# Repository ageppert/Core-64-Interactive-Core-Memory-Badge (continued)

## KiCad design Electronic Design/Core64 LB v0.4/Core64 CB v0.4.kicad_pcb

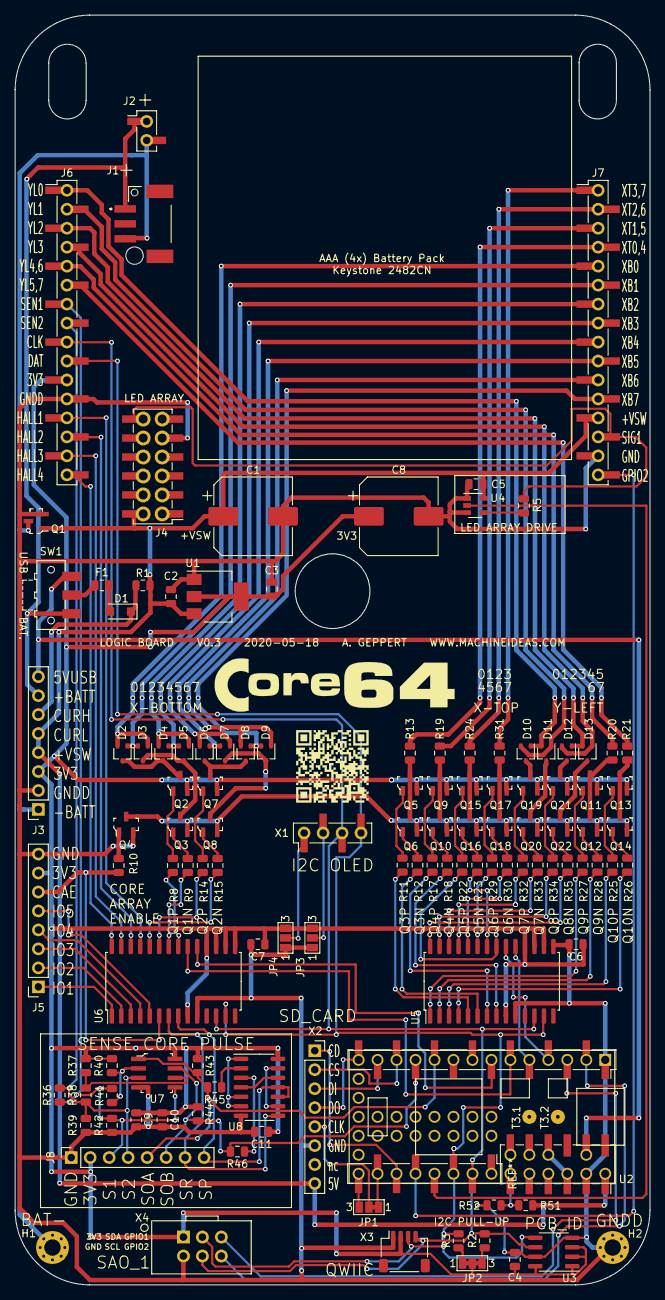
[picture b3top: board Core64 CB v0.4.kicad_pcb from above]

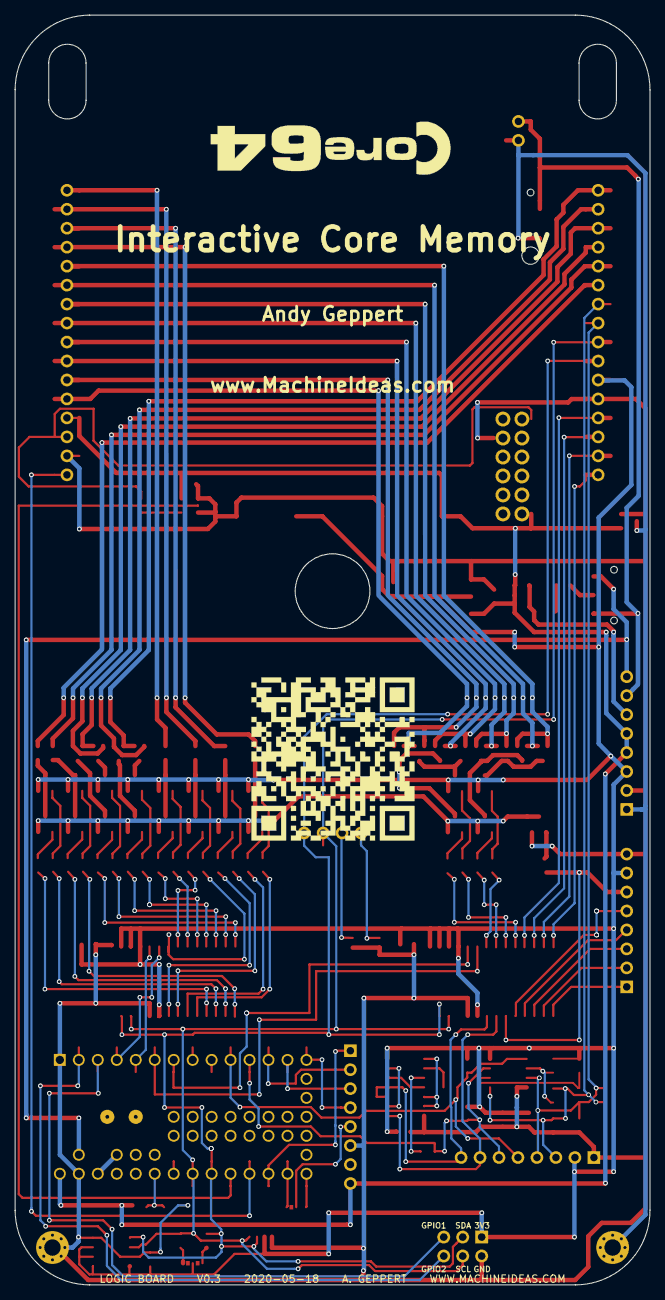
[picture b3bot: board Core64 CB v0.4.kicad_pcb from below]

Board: 2 copper layers, 85.0 x 170.0 mm, 122 parts (2 on the bottom side), 131 nets.

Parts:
C1, C8: 1000uF; CP_Elec_10x10
C2, C4, C5, C6, C7, C9, C11: 0.1uF; C_0805_2012Metric
C3, C10: 10uF; C_0805_2012Metric
D1: MBR120; D_SOD-123F
D2, D4, D6, D8, D10, D12: BAT54AW; SOT-323_SC-70
D3, D5, D7, D9, D11, D13: BAT54CW; SOT-323_SC-70
F1: Polyfuse; Fuse_0805_2012Metric
H1: -BATT PAD; MountingHole_2.2mm_M2_Pad_Via
H2: GND PAD; MountingHole_2.2mm_M2_Pad_Via
J1: BM03B-PASS-1-TFT__LF__SN_; BM03BPASS1TFTLFSN
J2: Conn_01x02_Male; PinSocket_1x02_P2.54mm_Vertical_SMD_Pin1Left
J3, J5, J8: Conn_01x08_Female; PinSocket_1x08_P2.54mm_Vertical
J4: TSM-106-03-T-DV‎; PinHeader_2x06_P2.54mm_Vertical_SMD_and_TH
J6, J7: SSW-116-22-F-S-VS‎; PinHeader_1x16_P2.54mm_Vertical_SMD_and_TH_Pin1Left
JP1: SolderJumper_3_Bridged12; SolderJumper-3_P1.3mm_Bridged12_Pad1.0x1.5mm_NumberLabels
JP2: SolderJumper_3_Bridged123; SolderJumper-3_P1.3mm_Bridged123_Pad1.0x1.5mm_NumberLabels
JP3, JP4: SolderJumper_3_Open; SolderJumper-3_P1.3mm_Open_Pad1.0x1.5mm_NumberLabels
L1, L2: Core_64_Logo; Core64_Logo
L3: Core_64_Github_Link; Github_Link_Large
L4: Core_64_Github_Link; Github_Link_Small
Q1: IRLML6344TRPBF; SOT-23-3
Q2, Q5, Q7, Q9, Q11, Q13, Q15, Q17, Q19, Q21: MMBT4403LT1G; SOT-23-3
Q3, Q4, Q6, Q8, Q10, Q12, Q14, Q16, Q18, Q20, Q22: MMBT4401LT1G; SOT-23-3
R1: 0.001; R_0805_2012Metric
R2, R3: 4K7; R_0805_2012Metric
R5: 300; R_0805_2012Metric
R8, R9, R10, R11, R12, R14, R15, R17, R18, R22, R23, R25, R26, R27, R28, R29, R30, R32, R33, R34, R35: 470; R_0805_2012Metric
R13, R19, R20, R21, R24, R31: 6R8; R_0805_2012Metric
R36, R39, R42: 1K5; R_0805_2012Metric
R37, R40: 1K8; R_0805_2012Metric
R38, R41: 11; R_0805_2012Metric
R43, R44, R45, R46, R51, R52: 10k; R_0805_2012Metric
SW1: JS102011SAQN; SW_SPDT_CK-JS102011SAQN
U1: LD1117S33TR_SOT223; SOT-223-3_TabPin2
U2: Teensy-LC; Teensy30_31_32_LC_SMD_SOCKETS
U3: M24C01-RMN; SOIC-8_3.9x4.9mm_P1.27mm
U4: SN74LV1T125DBVR; SOT-23-5
U5, U6: MCP23017_SO; SOIC-28W_7.5x17.9mm_P1.27mm
U7: LM393; SOIC-8_W3.9mm
U8: 74HC02; SOIC-14_3.9x8.7mm_P1.27mm
X1: SSW-104-22-L-S-VS; PinSocket_1x04_P2.54mm_Vertical_SMD_and_TH_Pin1Left
X2: Conn_01x08_Female; PinSocket_1x08_P2.54mm_Vertical
X3: Conn_01x04_Male; JST_SH_SM04B-SRSS-TB_1x04-1MP_P1.00mm_Horizontal
X4: SAO_conn_SFH11-NBPC-D03-ST-BK; Badgelife-SAOv169-BADGE-2x3

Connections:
3V3_800mA: C3.1, C4.1, C6.1, C7.1, C8.1, C9.1, C10.1, C11.1, J3.3, J5.7, J6.11, J8.2, JP2.2, JP3.3, JP4.3, Q2.2, Q5.2, Q7.2, Q9.2, Q11.2, Q13.2, Q15.2, Q17.2, Q19.2, Q21.2, R37.1, R40.1, R43.1, R44.1, U1.2, U3.1, U3.2, U3.3, U3.8, U5.9, U5.16, U5.17, U5.18, U6.9, U6.15, U6.16, U6.17, U6.18, U7.8, U8.14, X3.2, X4.1
5V_USB: J3.8, SW1.1, U2.34
+BATT: J1.1, J2.1, J3.7, SW1.3
+VSW: C1.1, C2.1, C5.1, J3.4, J3.5, J4.2, J7.13, Q1.1, R1.2, R51.1, U1.3, U2.33, U4.5, X2.8
-BATT: H1.1, J1.3, J2.2, J3.1, Q1.3
CUR_HI: D1.1, J3.6, R1.1
GNDPWR: Q3.2, Q4.3, Q6.2, Q8.2, Q10.2, Q12.2, Q14.2, Q16.2, Q18.2, Q20.2, Q22.2
HALL_SWITCH_1: J6.13, U6.25
HALL_SWITCH_2: J6.14, U6.26
HALL_SWITCH_3: J6.15, U6.27
HALL_SWITCH_4: J6.16, U6.28
I2C_CLOCK: J6.9, R2.2, U2.26, U3.6, U5.12, U6.12, X1.3, X3.4, X4.4
I2C_DATA: J6.10, R3.2, U2.25, U3.5, U5.13, U6.13, X1.4, X3.3, X4.3
IOEXP_ID32_INT_A: U2.4, U5.20
IOEXP_ID32_INT_B: U2.5, U5.19
IOEXP_ID33_INT_A: U2.6, U6.20
IOEXP_ID33_INT_B: U2.7, U6.19
LED_MATRIX_3V3_SIG: U2.24, U4.2
LED_MATRIX_+VSW_SIG: J4.12, J7.14, R5.2
unnamed: D1.2, F1.1
unnamed: D2.3, D4.3, Q2.3
unnamed: D3.3, D5.3, Q3.3
unnamed: D6.3, D8.3, Q7.3
unnamed: D7.3, D9.3, Q8.3
unnamed: D10.3, Q19.3
unnamed: D11.3, Q20.3
unnamed: D12.3, Q21.3
unnamed: D13.3, Q22.3
unnamed: F1.2, SW1.2
unnamed: JP1.1, U2.21
unnamed: JP1.3, U2.20
unnamed: JP2.1, R3.1
unnamed: JP2.3, R2.1
unnamed: JP3.2, X1.2
unnamed: JP4.2, X1.1
unnamed: Q2.1, R8.1
unnamed: Q3.1, R9.1
unnamed: Q4.1, R10.1
unnamed: Q5.1, R11.1
unnamed: Q5.3, Q6.3, R13.1
unnamed: Q6.1, R12.1
unnamed: Q7.1, R14.1
unnamed: Q8.1, R15.1
unnamed: Q9.1, R17.1
unnamed: Q10.1, R18.1
unnamed: Q9.3, Q10.3, R19.2
unnamed: Q11.1, R27.1
unnamed: Q11.3, Q12.3, R20.2
unnamed: Q12.1, R28.1
unnamed: Q13.1, R25.1
unnamed: Q13.3, Q14.3, R21.2
unnamed: Q14.1, R26.1
unnamed: Q15.1, R22.1
unnamed: Q15.3, Q16.3, R24.2
unnamed: Q16.1, R23.1
unnamed: Q17.1, R29.1
unnamed: Q17.3, Q18.3, R31.2
unnamed: Q18.1, R30.1
unnamed: Q19.1, R32.1
unnamed: Q20.1, R33.1
unnamed: Q21.1, R34.1
unnamed: Q22.1, R35.1
unnamed: R5.1, U4.4
unnamed: R37.2, R38.1, U7.6
unnamed: R40.2, R41.1, U7.2
unnamed: R45.1, U8.2
unnamed: R46.1, U8.3
unnamed: U8.1, U8.5, U8.6
unnamed: U8.4, U8.12
unnamed: U8.9, U8.13
Q1N: R9.2, U6.22
Q1P: R8.2, U6.21
Q2N: R15.2, U6.24
Q2P: R14.2, U6.23
Q3N: R12.2, U5.6
Q3P: R11.2, U5.5
Q4N: R18.2, U5.8
Q4P: R17.2, U5.7
Q5N: R23.2, U5.22
Q5P: R22.2, U5.21
Q6N: R30.2, U5.24
Q6P: R29.2, U5.23
Q7N: R33.2, U5.26
Q7P: R32.2, U5.25
Q8N: R35.2, U5.28
Q8P: R34.2, U5.27
Q9N: R28.2, U5.2
Q9P: R27.2, U5.1
Q10N: R26.2, U5.4
Q10P: R25.2, U5.3
SAO1_GPIO1(TX): U2.3, X4.5
SAO1_GPIO2(RX): U2.2, X4.6
SAO3_GPIO2: J7.16, U2.23
SD_CD: U2.22, X2.1
SD_CLK: JP1.2, X2.5
SD_CS: U2.12, X2.2
SD_DI: U2.13, X2.3
SD_DO: U2.14, X2.4
SENSE1: J6.7, J8.3, R36.1, R41.2, R42.1, U7.5
SENSE2: J6.8, J8.4, R36.2, R38.2, R39.1, U7.3
SENSE_OUT_A: J8.5, R43.2, R45.2, U2.10, U7.1
SENSE_OUT_B: J8.6, R44.2, R46.2, U2.11, U7.7
SENSE_PULSE: J8.8, U6.8, U8.10, U8.11
SENSE_RESET: J8.7, U6.7, U8.8
SPARE_1: J5.1, U6.1
SPARE_2: J5.2, U6.2
SPARE_3: J5.3, U6.3
SPARE_4: J5.4, U6.4
SPARE_5: J5.5, U6.5
TEENSY_3V3: U2.31, U2.35
TEENSY_GND: C1.2, C2.2, C3.2, C4.2, C5.2, C6.2, C7.2, C8.2, C9.2, C10.2, C11.2, H2.1, J3.2, J4.9, J5.8, J6.12, J7.15, J8.1, JP3.1, JP4.1, Q1.2, Q4.2, R39.2, R42.2, R52.2, U1.1, U2.1, U2.32, U3.4, U3.7, U4.1, U4.3, U5.10, U5.15, U6.10, U7.4, U8.7, X2.6, X3.1, X4.2
VSW_HALF_VOL_MONITOR: R51.2, R52.1, U2.28
WRITE_ENABLE: J5.6, R10.2, U6.6
XB0: D2.2, D3.1, J7.5
XB1: D2.1, D3.2, J7.6
XB2: D4.2, D5.1, J7.7
XB3: D4.1, D5.2, J7.8
XB4: D6.2, D7.1, J7.9
XB5: D6.1, D7.2, J7.10
XB6: D8.2, D9.1, J7.11
XB7: D8.1, D9.2, J7.12
XT0-4: J7.4, R13.2
XT1-5: J7.3, R19.1
XT2-6: J7.2, R24.1
XT3-7: J7.1, R31.1
YL0: D10.1, D11.2, J6.1
YL1: D10.2, D11.1, J6.2
YL2: D12.1, D13.2, J6.3
YL3: D12.2, D13.1, J6.4
YL4: J6.5, R20.1
YL5: J6.6, R21.1

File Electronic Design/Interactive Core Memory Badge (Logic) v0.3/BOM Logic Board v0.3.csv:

Source:,/Users/ageppert/Dropbox/Electronics/Core 64 Interactive Badge/Core-64-Interactive-Core-Memory-Badge/Electronic Design/Interactive Core Memory Badge (Logic) v0.3/Interactive Core Memory Badge (Logic) Main v0.3.sch,,,,,,,,,,,,,,,,,
Date:,"Thursday, May 21, 2020 at 07:06:58 AM",,,,,,,,,,,,,,,,,
Tool:,Eeschema (5.1.2-1)-1,,,,,,,,,,,,,,,,,
Generator:,/private/var/folders/kh/1q_kd4hn7cq821df7xpmdhbw0000gn/T/AppTranslocation/C0C9017D-E73E-48F9-99F9-451879B2E2B1/d/kicad.app/Contents/SharedSupport/plugins/bom_csv_grouped_by_value.py,,,,,,,,,,,,,,,,,
Component Count:,122,,,,,,,,,,,,,,,,,
,,,,,,,,,,,,,,,,,,
,,,,,,,,,,,,,,,,,,
Collated Components:,,,,,,,,,,,,,,,,,,
,,,,,,,,,,,,,,,,,,
Item,Qty,Reference(s),Value,Digi-Key_PN,LibPart,Footprint,Datasheet,Category,DK_Datasheet_Link,DK_Detail_Page,Description,Family,Height,MPN,Manufacturer,Manufacturer_Name,Manufacturer_Part_Number,Status
1,2,"C1, C8",1000uF,,Device:CP1_Small,Capacitor_SMD:CP_Elec_10x10,~,,,,,,,,,,,
2,7,"C2, C4, C5, C6, C7, C9, C11",0.1uF,,Device:CP1_Small,Capacitor_SMD:C_0805_2012Metric,~,,,,,,,,,,,
3,2,"C3, C10",10uF,,Device:CP1_Small,Capacitor_SMD:C_0805_2012Metric,~,,,,,,,,,,,
4,1,D1,MBR120,,Diode:MBR0520,Diode_SMD:D_SOD-123F,https://www.digikey.com/product-detail/en/on-semiconductor/M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,,,,,,,,,,,
5,6,"D2, D4, D6, D8, D10, D12",BAT54AW,,Diode:BAT54AW,Package_TO_SOT_SMD:SOT-323_SC-70,https://assets.nexperia.com/documents/data-sheet/BAT54W_SER.pdf,,,,,,,,,,,
6,6,"D3, D5, D7, D9, D11, D13",BAT54CW,,Diode:BAT54CW,Package_TO_SOT_SMD:SOT-323_SC-70,https://assets.nexperia.com/documents/data-sheet/BAT54W_SER.pdf,,,,,,,,,,,
7,1,F1,Polyfuse,,Device:Polyfuse,Fuse:Fuse_0805_2012Metric,~,,,,,,,,,,,
8,1,H1,#NAME?,,Mechanical:MountingHole_Pad,MountingHole:MountingHole_2.2mm_M2_Pad_Via,~,,,,,,,,,,,
9,1,H2,GND PAD,,Mechanical:MountingHole_Pad,MountingHole:MountingHole_2.2mm_M2_Pad_Via,~,,,,,,,,,,,
10,1,J1,BM03B-PASS-1-TFT__LF__SN_,,BM03B-PASS-1-TFT__LF__SN_:BM03B-PASS-1-TFT__LF__SN_,JST_BM03B-PASS-1-TFT:BM03BPASS1TFTLFSN,http://www.jst-mfg.com/product/pdf/eng/ePA-F.pdf,,,,Conn Shrouded Header HDR 3 POS 2mm Solder ST SMD T/R,,8.8,,,JST (JAPAN SOLDERLESS TERMINALS),BM03B-PASS-1-TFT (LF)(SN),
11,1,J2,Conn_01x02_Male,,Connector:Conn_01x02_Male,Connector_PinSocket_2.54mm:PinSocket_1x02_P2.54mm_Vertical_SMD_Pin1Left,~,,,,,,,,,,,
12,4,"J3, J5, J8, X2",Conn_01x08_Female,,Connector:Conn_01x08_Female,Connector_PinSocket_2.54mm:PinSocket_1x08_P2.54mm_Vertical,~,,,,,,,,,,,
13,1,J4,TSM-106-03-T-DV‎,,Connector_Generic:Conn_02x06_Odd_Even,Connector_PinHeader_2.54mm:PinHeader_2x06_P2.54mm_Vertical_SMD_and_TH,~,,,,,,,,,,,
14,2,"J6, J7",SSW-116-22-F-S-VS‎,,Connector:Conn_01x16_Female,Connector_PinHeader_2.54mm:PinHeader_1x16_P2.54mm_Vertical_SMD_and_TH_Pin1Left,~,,,,,,,,,,,
15,1,JP1,SolderJumper_3_Bridged12,,Jumper:SolderJumper_3_Bridged12,Jumper:SolderJumper-3_P1.3mm_Bridged12_Pad1.0x1.5mm_NumberLabels,~,,,,,,,,,,,
16,1,JP2,SolderJumper_3_Bridged123,,Jumper:SolderJumper_3_Bridged123,Jumper:SolderJumper-3_P1.3mm_Bridged123_Pad1.0x1.5mm_NumberLabels,~,,,,,,,,,,,
17,2,"JP3, JP4",SolderJumper_3_Open,,Jumper:SolderJumper_3_Open,Jumper:SolderJumper-3_P1.3mm_Open_Pad1.0x1.5mm_NumberLabels,~,,,,,,,,,,,
18,2,"L1, L2",Core_64_Logo,,CORE_64_LIBRARY:Core_64_Logo,Core_Memory_8x8_Array:Core64_Logo,,,,,,,,,,,,
19,1,L3,Core_64_Github_Link,,CORE_64_LIBRARY:Core_64_Github_Link,Core_Memory_8x8_Array:Github_Link_Large,,,,,,,,,,,,
20,1,L4,Core_64_Github_Link,,CORE_64_LIBRARY:Core_64_Github_Link,Core_Memory_8x8_Array:Github_Link_Small,,,,,,,,,,,,
21,1,Q1,IRLML6344TRPBF,,Transistor_FET:IRLML2060,Digikey:SOT-23-3,https://www.digikey.com/product-detail/en/infineon-technolog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,,,,,,,,,,,
22,10,"Q2, Q5, Q7, Q9, Q11, Q13, Q15, Q17, Q19, Q21",MMBT4403LT1G,MMBT4403LT1GOSCT-ND,Digikey-Transistors:MMBT4403LT1G,Digikey:SOT-23-3,http://www.onsemi.com/pub/Collateral/MMBT4403LT1-D.PDF,Discrete Semiconductor Products,http://www.onsemi.com/pub/Collateral/MMBT4403LT1-D.PDF,/product-detail/en/on-semiconductor/MMBT4403LT1G/MMBT4403LT1GOSCT-ND/1139820,TRANS PNP 40V 0.6A SOT23,Transistors - Bipolar (BJT) - Single,,MMBT4403LT1G,ON Semiconductor,,,Active
23,11,"Q3, Q4, Q6, Q8, Q10, Q12, Q14, Q16, Q18, Q20, Q22",MMBT4401LT1G,MMBT4401LT1GOSCT-ND,Digikey-Transistors:MMBT4401LT1G,Digikey:SOT-23-3,http://www.onsemi.com/pub/Collateral/MMBT4401LT1-D.PDF,Discrete Semiconductor Products,http://www.onsemi.com/pub/Collateral/MMBT4401LT1-D.PDF,/product-detail/en/on-semiconductor/MMBT4401LT1G/MMBT4401LT1GOSCT-ND/1139819,TRANS NPN 40V 0.6A SOT23,Transistors - Bipolar (BJT) - Single,,MMBT4401LT1G,ON Semiconductor,,,Active
24,1,R1,0.001,,Device:R,Resistor_SMD:R_0805_2012Metric,~,,,,,,,,,,,
25,2,"R2, R3",4K7,,Device:R,Resistor_SMD:R_0805_2012Metric,~,,,,,,,,,,,
26,1,R5,300,,Device:R,Resistor_SMD:R_0805_2012Metric,~,,,,,,,,,,,
27,21,"R8, R9, R10, R11, R12, R14, R15, R17, R18, R22, R23, R25, R26, R27, R28, R29, R30, R32, R33, R34, R35",470,,Device:R,Resistor_SMD:R_0805_2012Metric,~,,,,,,,,,,,
28,6,"R13, R19, R20, R21, R24, R31",6R8,,Device:R,Resistor_SMD:R_0805_2012Metric,~,,,,,,,,,,,
29,3,"R36, R39, R42",1K5,,Device:R,Resistor_SMD:R_0805_2012Metric,~,,,,,,,,,,,
30,2,"R37, R40",1K8,,Device:R,Resistor_SMD:R_0805_2012Metric,~,,,,,,,,,,,
31,2,"R38, R41",11,,Device:R,Resistor_SMD:R_0805_2012Metric,~,,,,,,,,,,,
32,6,"R43, R44, R45, R46, R51, R52",10k,,Device:R,Resistor_SMD:R_0805_2012Metric,~,,,,,,,,,,,
33,1,SW1,JS102011SAQN,,Switch:SW_SPDT,Button_Switch_SMD:SW_SPDT_CK-JS102011SAQN,~,,,,,,,,,,,
34,1,U1,LD1117S33TR_SOT223,,Regulator_Linear:LD1117S33TR_SOT223,Package_TO_SOT_SMD:SOT-223-3_TabPin2,http://www.st.com/st-web-ui/static/active/en/resource/techni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,,,,,,,,,,,
35,1,U2,Teensy-LC,,Teensy:Teensy-LC,Teensy:Teensy30_31_32_LC_SMD_SOCKETS,,,,,,,,,,,,
36,1,U3,M24C01-RMN,,Memory_EEPROM:M24C01-RMN,Package_SO:SOIC-8_3.9x4.9mm_P1.27mm,http://www.st.com/content/ccc/resource/technical/document/da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,,,,,,,,,,,
37,1,U4,SN74LV1T125DBVR,,Logic_LevelTranslator:SN74LV1T125DBVR,Package_TO_SOT_SMD:SOT-23-5,http://www.ti.com/lit/ds/symlink/sn74lv1t125.pdf,,,,,,,,,,,
38,2,"U5, U6",MCP23017_SO,,Interface_Expansion:MCP23017_SO,Package_SO:SOIC-28W_7.5x17.9mm_P1.27mm,http://ww1.microchip.com/downloads/en/DeviceDoc/20001952C.pdf,,,,,,,,,,,
39,1,U7,LM393,,Comparator:LM393,Digikey:SOIC-8_W3.9mm,http://www.ti.com/lit/ds/symlink/lm393-n.pdf,,,,,,,,,,,
40,1,U8,74HC02,,74xx:74HC02,Package_SO:SOIC-14_3.9x8.7mm_P1.27mm,http://www.ti.com/lit/gpn/sn74hc02,,,,,,,,,,,
41,1,X1,SSW-104-22-L-S-VS,,Connector:Conn_01x04_Female,Connector_PinSocket_2.54mm:PinSocket_1x04_P2.54mm_Vertical_SMD_and_TH_Pin1Left,~,,,,,,,,,,,
42,1,X3,Conn_01x04_Male,,Connector:Conn_01x04_Male,Connector_JST:JST_SH_SM04B-SRSS-TB_1x04-1MP_P1.00mm_Horizontal,~,,,,,,,,,,,
43,1,X4,SAO_conn_SFH11-NBPC-D03-ST-BK,,badgelife_shitty_addon_v169bis:SAO_conn_SFH11-NBPC-D03-ST-BK,badgelife_sao_v169bis:Badgelife-SAOv169-BADGE-2x3,,,,,,,,,,,,

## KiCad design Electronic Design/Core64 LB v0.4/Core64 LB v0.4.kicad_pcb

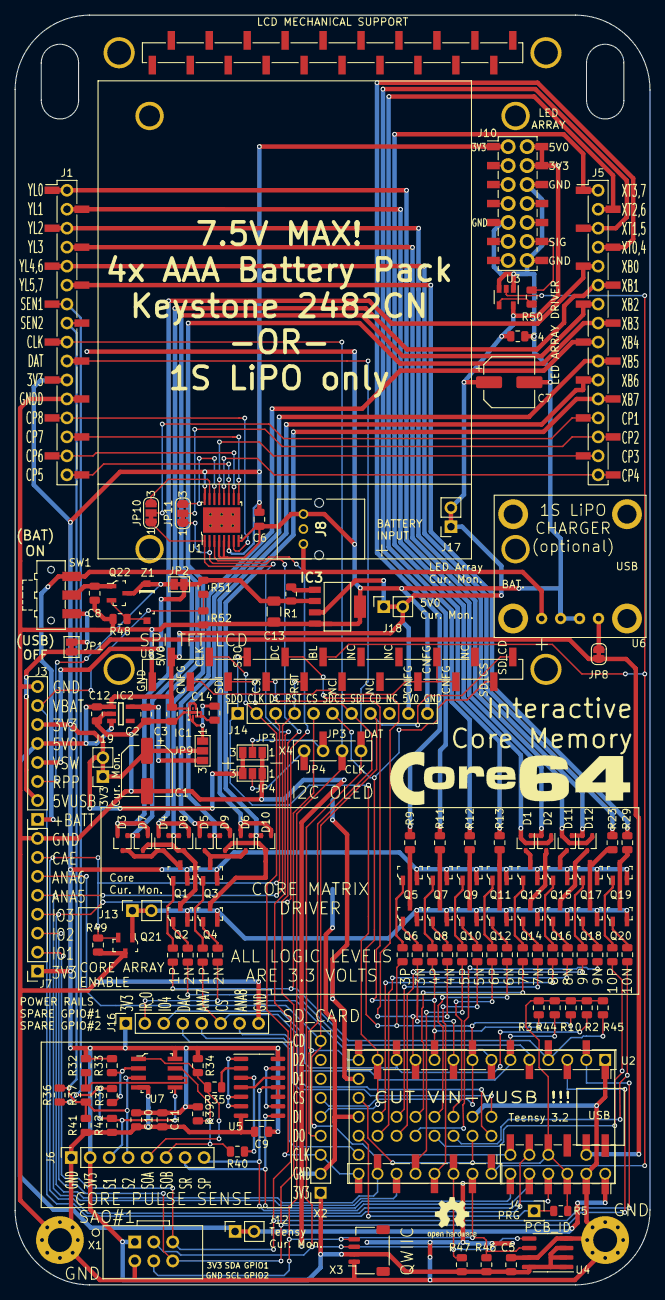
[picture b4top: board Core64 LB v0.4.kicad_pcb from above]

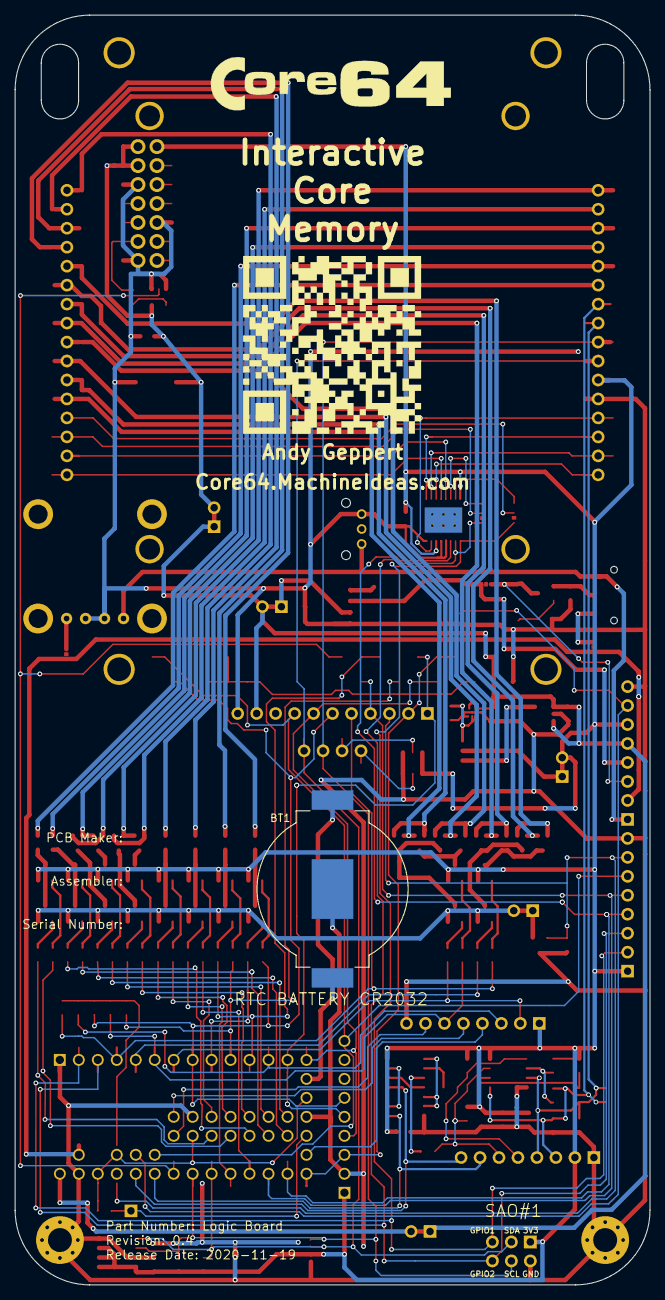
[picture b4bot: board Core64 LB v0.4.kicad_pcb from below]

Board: 2 copper layers, 85.0 x 170.0 mm, 146 parts (3 on the bottom side), 135 nets.

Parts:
BT1: 3V; BatteryHolder_MPD_BC2003_1x2032
C1, C7: 470uF; CP_Elec_6.3x7.7
C2, C3, C12, C14: 1uF; C_0805_2012Metric
C4, C5, C6, C9, C10: 0.1uF; C_0805_2012Metric
C8: 0.01uF; C_0805_2012Metric
C11: 10uF; C_0805_2012Metric
C13: 68uF; C_1206_3216Metric
D1, D3, D4, D5, D6, D11: BAT54AW; SOT-323_SC-70
D2, D7, D8, D9, D10, D12: BAT54CW; SOT-323_SC-70
H1, H2: GND PAD; MountingHole_3.2mm_M3_Pad_Via
IC1: NCP176AMX330TCG
IC2: TPS7A0533PDBVR; SOT95P280X145-5N
IC3: LP3961EMP-5.0; SOT150P696X180-5N
J1, J5: SSW-116-22-F-S-VS‎; PinHeader_1x16_P2.54mm_Vertical_SMD_and_TH_Pin1Left
J3: Conn_01x08_Female; PinSocket_1x08_P2.54mm_Vertical
J4: PRG; PinSocket_1x01_P2.54mm_Vertical
J6, J7, J16: HEADER_8-PIN_0.1; PinSocket_1x08_P2.54mm_Vertical
J8: S03B-PASK-2_LF__SN_; S03BPASK2LFSN
J10: TSM-106-03-T-DV‎; PinHeader_2x07_P2.54mm_Vertical_SMD_and_TH
J12: TEENSY Cur. Mon.; PinSocket_1x02_P2.54mm_Vertical
J13: Core Cur. Mon.; PinSocket_1x02_P2.54mm_Vertical
J14: HEADER_11-PIN_0.1; PinSocket_1x11_P2.54mm_Vertical
J17: LED Cur. Mon.; PinSocket_1x02_P2.54mm_Vertical
J18: 5V0 Cur. Mon.; PinSocket_1x02_P2.54mm_Vertical
J19: 3V3 Cur. Mon.; PinSocket_1x02_P2.54mm_Vertical
JP1: USB_Power_Enable; SolderJumper-2_P1.3mm_Bridged_Pad1.0x1.5mm
JP2: Opt. Cur. Mon.; SolderJumper-2_P1.3mm_Bridged_Pad1.0x1.5mm
JP3, JP4: SolderJumper_3_Open; SolderJumper-3_P1.3mm_Open_Pad1.0x1.5mm_NumberLabels
JP8: Teensy_Charge_Enable; SolderJumper-2_P1.3mm_Bridged_RoundedPad1.0x1.5mm
JP9: 3V3_Select; SolderJumper-3_P1.3mm_Open_Pad1.0x1.5mm_NumberLabels
JP10, JP11: SolderJumper_3_Open; SolderJumper-3_P1.3mm_Bridged12_RoundedPad1.0x1.5mm_NumberL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
L1, L2: Core_64_Logo; Core64_Logo
L3: Core_64_MachineIdeas_Link; Core64_QR_Link_MachineIdeas
L4: Logo_Open_Hardware_Small; OSHW-Logo2_7.3x6mm_SilkScreen
Q1, Q3, Q5, Q7, Q9, Q11, Q13, Q15, Q17, Q19: MMBT4403LT1G; SOT-23-3
Q2, Q4, Q6, Q8, Q10, Q12, Q14, Q16, Q18, Q20: MMBT4401LT1G; SOT-23-3
Q21: Q_NMOS_DGS_NVTR4503NT1G; SOT-23-3
Q22: MCC_SL3401A; SOT-23-3
R1, R34, R35, R39, R40, R48, R49: 10k; R_0805_2012Metric
R2, R3, R5, R10, R44, R45: 10K; R_0805_2012Metric
R4, R6, R7, R8, R14, R15, R16, R17, R18, R19, R20, R21, R22, R24, R25, R26, R27, R28, R30, R31, R50: 470; R_0805_2012Metric
R9, R11, R12, R13, R23, R29: 6R8; R_0805_2012Metric
R32, R33: 1K8; R_0805_2012Metric
R36, R41, R42: 1K5; R_0805_2012Metric
R37, R38: 11; R_0805_2012Metric
R46, R47: 2K2; R_0805_2012Metric
R51: 33k; R_0805_2012Metric
R52: 11k; R_0805_2012Metric
SW1: JS102011SAQN; SW_SPDT_CK-JS102011SAQN
U1: 74HC238; TSSOP-16-1EP_W4.40mm
U2: Teensy3.2; Teensy30_31_32_LC_SMD_SOCKETS
U3: SN74LV1T125DBVR; SOT-23-5
U4: M24C01-RMN; SOIC-8_3.9x4.9mm_P1.27mm
U5: 74HC02; SOIC-14_3.9x8.7mm_P1.27mm
U6: Micro_LiPo_Charger
U7: LM393; SOIC-8_W3.9mm
U8: Adafruit_3.2_TFT_1743; Adafruit_3.2_TFT_Dual_PinHeader_1x20_P2.54mm_Vertical_SMD_P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
X1: SAO_conn_SFH11-NBPC-D03-ST-BK; Badgelife-SAOv169-BADGE-2x3
X2: Header_9-PIN_0.1; PinSocket_1x09_P2.54mm_Vertical
X3: QWIIC; JST_SH_SM04B-SRSS-TB_1x04-1MP_P1.00mm_Horizontal
X4: SSW-104-22-L-S-VS; PinSocket_1x04_P2.54mm_Vertical_SMD_and_TH_Pin1Left
Z1: PDZ10BGWX_(10V); SOD-123

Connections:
3V3: C1.1, C5.1, C6.1, C9.1, C10.1, C11.1, J1.11, J3.6, J6.2, J7.1, J10.1, J16.1, J19.1, J19.2, JP3.3, JP4.3, JP9.2, Q1.2, Q3.2, Q5.2, Q7.2, Q9.2, Q11.2, Q13.2, Q15.2, Q17.2, Q19.2, R32.1, R33.1, R34.1, R39.1, R46.1, R47.1, U1.6, U1.16, U4.1, U4.2, U4.3, U4.8, U5.14, U7.8, X1.1, X2.1, X3.2
5V0: C3.1, C4.1, C7.1, C12.1, IC1.4, IC1.6, IC2.1, IC2.3, IC3.3, J3.5, J10.2, J10.4, J12.1, J12.2, J14.10, J17.1, J17.2, J18.1, J18.2, U2.33, U3.5, U8.2
+BATT: J3.1, J8.1, SW1.1, U6.4
+RPP: J3.3, JP2.1, Q22.3, Z1.1
+VSW: C13.1, IC3.2, J3.4, JP2.2, R1.1, R51.1
-BATT: BT1.2, C1.2, C2.2, C3.2, C4.2, C5.2, C6.2, C7.2, C8.2, C9.2, C10.2, C11.2, C12.2, C13.2, C14.2, H1.1, H2.1, IC1.3, IC1.7, IC2.2, IC3.4, IC3.5, J1.12, J3.8, J6.1, J7.8, J8.3, J10.6, J10.9, J10.14, J14.11, J16.8, JP3.1, JP4.1, Q21.3, R41.2, R42.2, R48.2, R49.1, R52.2, U1.4, U1.5, U1.8, U2.1, U2.17, U2.32, U2.39, U3.1, U3.3, U4.4, U4.7, U5.7, U6.2, U6.3, U7.4, U8.1, X1.2, X2.2, X3.1
CP1_EN: J5.13, JP10.2
CP2_EN: J5.14, JP11.2
CP3_EN: J5.15, U1.13
CP4_EN: J5.16, U1.12
CP5_EN: J1.16, U1.11
CP6_EN: J1.15, U1.10
CP7_EN: J1.14, U1.9
CP8_EN: J1.13, U1.7
GNDPWR: J13.1, J13.2, Q2.2, Q4.2, Q6.2, Q8.2, Q10.2, Q12.2, Q14.2, Q16.2, Q18.2, Q20.2, Q21.1
I2C_CLOCK: J1.9, R46.2, U2.26, U4.6, X1.4, X3.4, X4.3
I2C_DATA: J1.10, R47.2, U2.25, U4.5, X1.3, X3.3, X4.4
IR_OUT: J16.2, R28.2, U2.7
LED_ARRAY_3V3_SIG: U2.27, U3.2, U8.10
LED_ARRAY_5V0_SIG: J10.12, R50.1
unnamed: BT1.1, U2.15
unnamed: C2.1, IC2.5, JP9.3
unnamed: C8.1, Q22.1, SW1.2
unnamed: C14.1, IC1.1, IC1.2, JP9.1
unnamed: D1.3, Q13.3
unnamed: D2.3, Q14.3
unnamed: D3.3, D4.3, Q1.3
unnamed: D5.3, D6.3, Q3.3
unnamed: D7.3, D8.3, Q2.3
unnamed: D9.3, D10.3, Q4.3
unnamed: D11.3, Q15.3
unnamed: D12.3, Q16.3
unnamed: IC3.1, R1.2
unnamed: J4.1, R5.2, U2.18
unnamed: JP1.1, SW1.3
unnamed: JP3.2, X4.2
unnamed: JP4.2, X4.1
unnamed: JP8.2, U6.1
unnamed: JP10.3, U1.15
unnamed: JP11.3, U1.14
unnamed: Q1.1, R21.1
unnamed: Q2.1, R27.1
unnamed: Q3.1, R22.1
unnamed: Q4.1, R28.1
unnamed: Q5.1, R4.1
unnamed: Q5.3, Q6.3, R9.1
unnamed: Q6.1, R14.1
unnamed: Q7.1, R6.1
unnamed: Q7.3, Q8.3, R11.2
unnamed: Q8.1, R15.1
unnamed: Q9.1, R7.1
unnamed: Q10.1, R16.1
unnamed: Q9.3, Q10.3, R12.2
unnamed: Q11.1, R8.1
unnamed: Q11.3, Q12.3, R13.2
unnamed: Q12.1, R17.1
unnamed: Q13.1, R18.1
unnamed: Q14.1, R20.1
unnamed: Q15.1, R25.1
unnamed: Q16.1, R31.1
unnamed: Q17.1, R19.1
unnamed: Q17.3, Q18.3, R23.2
unnamed: Q18.1, R24.1
unnamed: Q19.1, R26.1
unnamed: Q19.3, Q20.3, R29.2
unnamed: Q20.1, R30.1
unnamed: Q22.2, R48.1, Z1.2
unnamed: R32.2, R37.1, U7.6
unnamed: R33.2, R38.1, U7.2
unnamed: R35.1, U5.2
unnamed: R40.1, U5.3
unnamed: R50.2, U3.4
unnamed: U5.1, U5.5, U5.6
unnamed: U5.4, U5.12
unnamed: U5.9, U5.13
unnamed: U8.3, U8.15, U8.16, U8.17
OLED_SPI_CS: J14.5, R21.2, R45.2, U2.4
OLED_SPI_DC: J7.7, J14.3, Q21.2, R49.2, U2.30
Q1N: R27.2, U2.5
Q2P: J16.6, R22.2, R44.2, U2.6
Q3N: R14.2, U2.9
Q3P: J14.6, R4.2, R10.2, U2.8, U8.19, X2.6
Q4N: R15.2, U2.11, U8.8
Q4P: R3.2, R6.2, U2.10, U8.7
Q5N: R16.2, U2.24
Q5P: R7.2, U2.23
Q6N: R17.2, U2.41
Q6P: R8.2, U2.40
Q7N: R20.2, U2.43
Q7P: R18.2, U2.42
Q8N: R31.2, U2.45
Q8P: R25.2, U2.44
Q9N: R24.2, U2.47
Q9P: R19.2, U2.46
Q10N: R30.2, U2.49
Q10P: R26.2, U2.48
SAO_G1_or_SPARE_1_or_CP_ADDR_0: J7.2, JP10.1, U1.1, U2.2, X1.5
SAO_G2_or_SPARE_2_or_CP_ADDR_1: J7.3, JP11.1, U1.2, U2.3, X1.6
SD_SPI_CD: J7.6, J14.8, U2.37, U8.20, X2.9
SENSE1: J1.7, J6.3, R36.1, R38.2, R42.1, U7.5
SENSE2: J1.8, J6.4, R36.2, R37.2, R41.1, U7.3
SENSE_OUT_A: J6.5, R34.2, R35.2, U7.1
SENSE_OUT_B: J6.6, R39.2, R40.2, U7.7
SENSE_PULSE: J6.8, U2.29, U5.10, U5.11
SENSE_RESET: J6.7, U2.28, U5.8
SPARE_3_or_CP_ADDR_2: J7.4, U1.3, U2.21
SPARE_4_IR_IN: J16.3, R2.2, U2.12
SPARE_5: J7.5, J14.4, U2.22, U8.9
SPARE_ADC_DAC: J16.4, U2.19
SPARE_ANA_7: J16.5, U2.38
SPARE_ANA_8: J16.7, U2.51
SPI_CLK: J14.2, U2.20, U8.4, X2.3
SPI_SDI: J14.7, U2.14, U8.5, X2.4
SPI_SDO: J14.1, U2.13, U8.6, X2.5
TEENSY_3V3: R2.1, R3.1, R5.1, R10.1, R44.1, R45.1, U2.16, U2.31, U2.35, U2.50
TEENSY_VUSB: J3.2, JP1.2, JP8.1, U2.34
VBAT_MON: J3.7, R51.2, R52.1, U2.36
XB0: D3.2, D7.1, J5.5
XB1: D3.1, D7.2, J5.6
XB2: D4.2, D8.1, J5.7
XB3: D4.1, D8.2, J5.8
XB4: D5.2, D9.1, J5.9
XB5: D5.1, D9.2, J5.10
XB6: D6.2, D10.1, J5.11
XB7: D6.1, D10.2, J5.12
XT0,4: J5.4, R9.2
XT1,5: J5.3, R11.1
XT2,6: J5.2, R12.1
XT3,7: J5.1, R13.1
YL0: D1.1, D2.2, J1.1
YL1: D1.2, D2.1, J1.2
YL2: D11.1, D12.2, J1.3
YL3: D11.2, D12.1, J1.4
YL4: J1.5, R23.1
YL5: J1.6, R29.1

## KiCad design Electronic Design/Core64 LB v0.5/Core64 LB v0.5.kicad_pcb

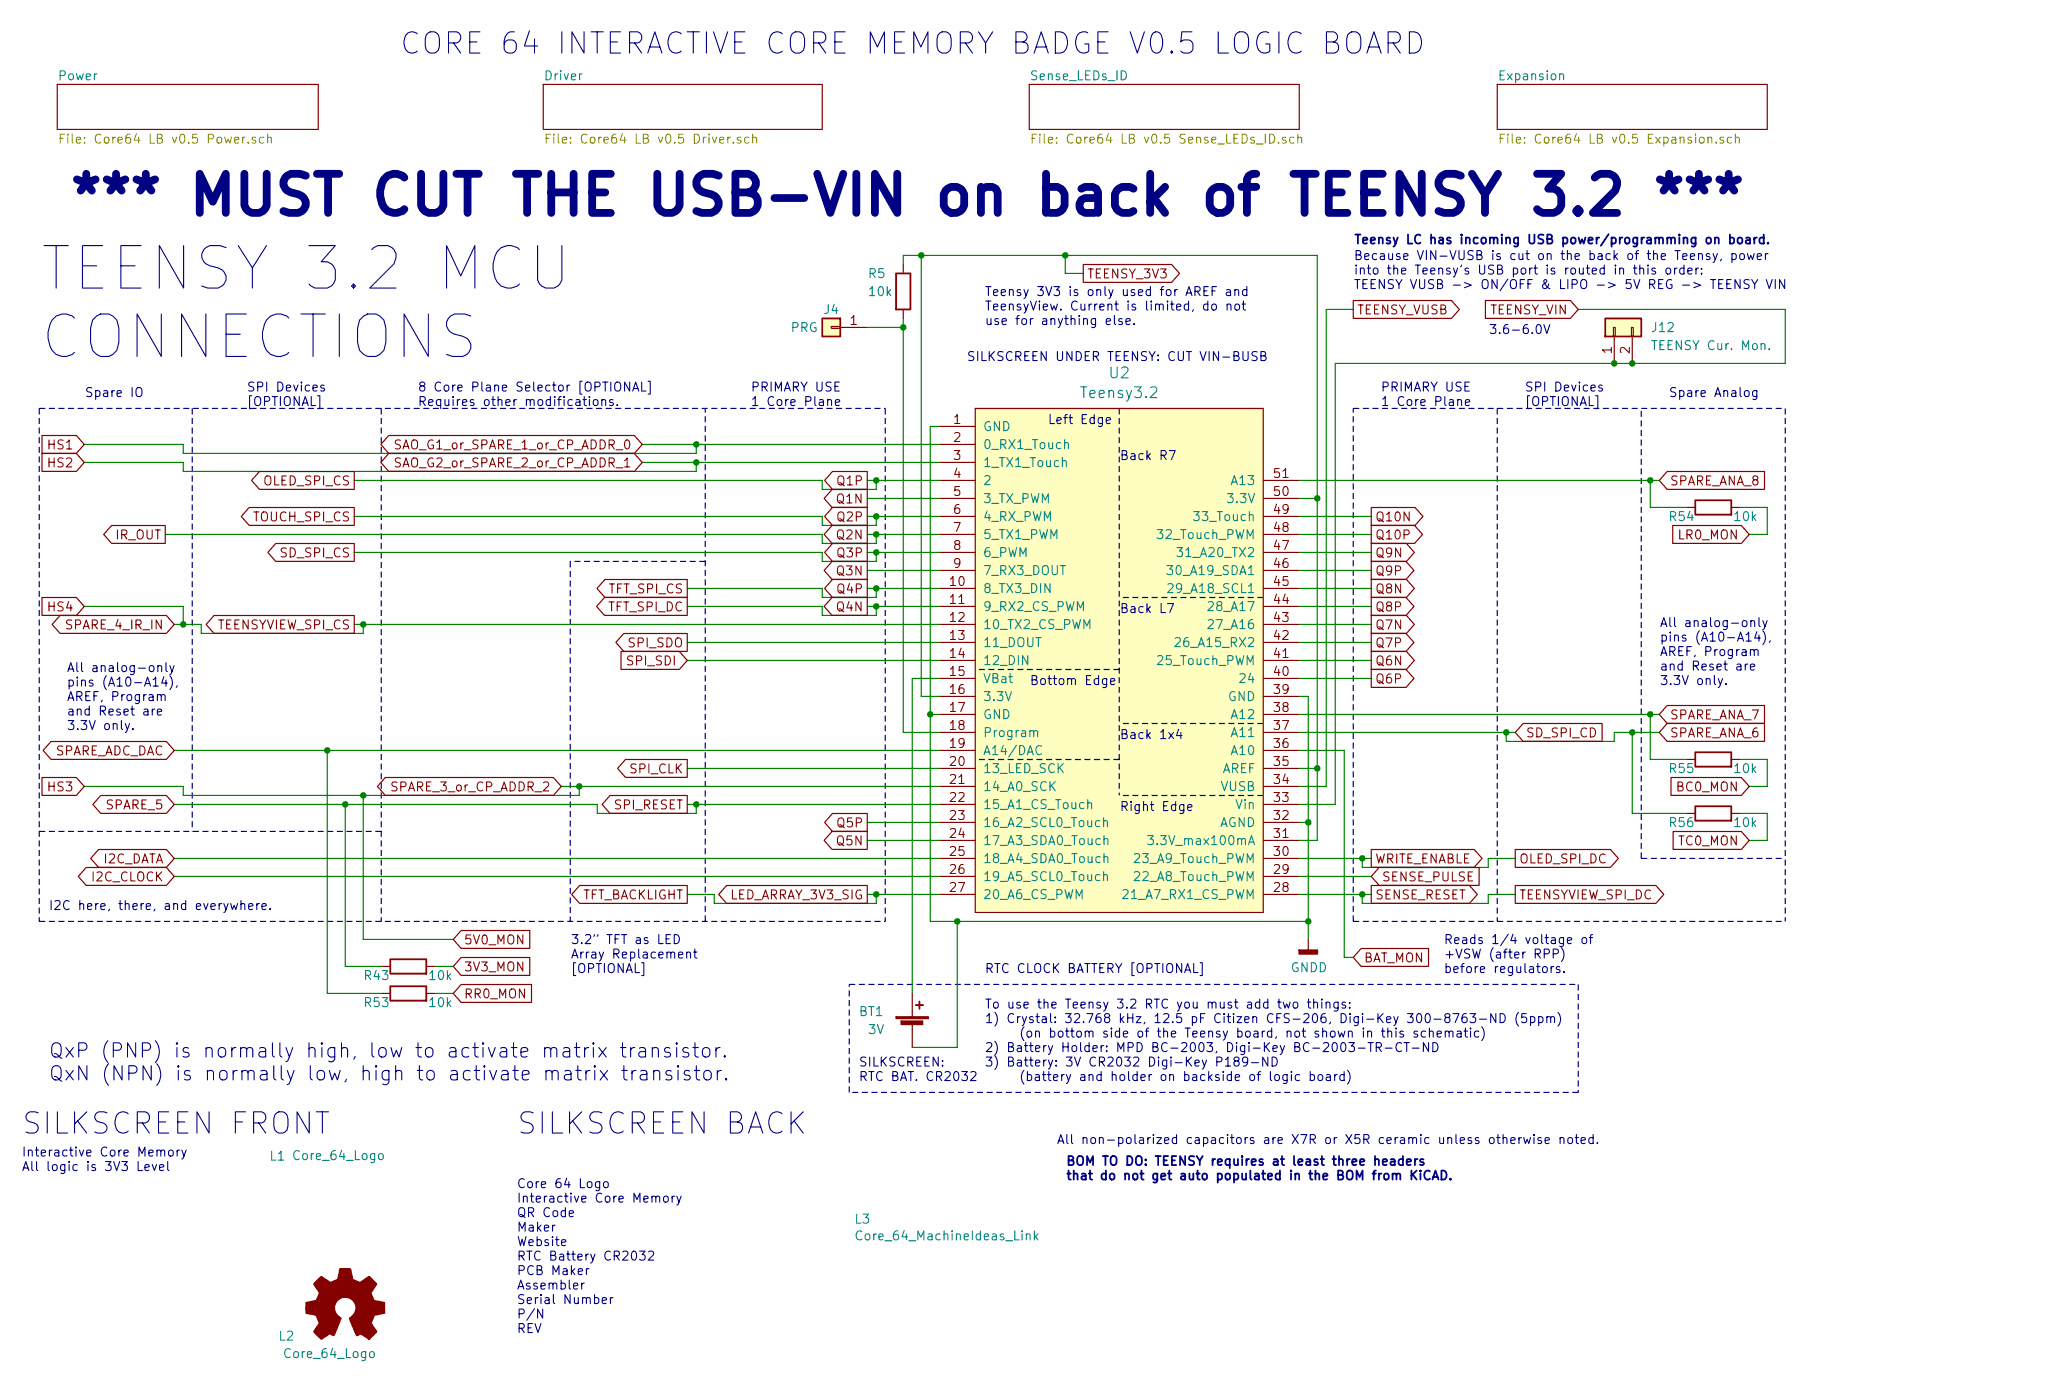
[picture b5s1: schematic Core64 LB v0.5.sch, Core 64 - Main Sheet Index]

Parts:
BT1: 3V; BatteryHolder_MPD_BC2003_1x2032
J4: PRG; PinSocket_1x01_P2.54mm_Vertical
J12: TEENSY Cur. Mon.; PinSocket_1x02_P2.54mm_Vertical
L1, L2: Core_64_Logo; Core64_Logo
L3: Core_64_MachineIdeas_Link; Core64_QR_Link_MachineIdeas
L4: Logo_Open_Hardware_Small; OSHW-Logo2_7.3x6mm_SilkScreen
R5, R43, R53, R54, R55, R56: 10k; R_0805_2012Metric
U2: Teensy3.2; Teensy30_31_32_LC_SMD_SOCKETS

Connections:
3V3: R43.2; also elsewhere on the board
5V0: J12.1, J12.2, U2.33 (Vin); also elsewhere on the board
5V0_MON: U2.21 (14_A0_SCK); also elsewhere on the board
BAT_MON: U2.36 (A10); also elsewhere on the board
BC0_MON: R55.2; also elsewhere on the board
HS1: U2.2 (0_RX1_Touch); also elsewhere on the board
HS2: U2.3 (1_TX1_Touch); also elsewhere on the board
HS4: U2.12 (10_TX2_CS_PWM); also elsewhere on the board
I2C_CLOCK: U2.26 (19_A5_SCL0_Touch); also elsewhere on the board
I2C_DATA: U2.25 (18_A4_SDA0_Touch); also elsewhere on the board
IR_OUT: U2.7 (5_TX1_PWM); also elsewhere on the board
LR0_MON: R54.2; also elsewhere on the board
unnamed: BT1.1 (+), U2.15 (VBat)
unnamed: J4.1, R5.2, U2.18 (Program)
OLED_SPI_CS: U2.4 (2); also elsewhere on the board
OLED_SPI_DC: U2.30 (23_A9_Touch_PWM); also elsewhere on the board
Q1N: U2.5 (3_TX_PWM); also elsewhere on the board
Q2P: U2.6 (4_RX_PWM); also elsewhere on the board
Q3N: U2.9 (7_RX3_DOUT); also elsewhere on the board
Q3P: U2.8 (6_PWM); also elsewhere on the board
Q4N: U2.11 (9_RX2_CS_PWM); also elsewhere on the board
Q4P: U2.10 (8_TX3_DIN); also elsewhere on the board
Q5N: U2.24 (17_A3_SDA0_Touch); also elsewhere on the board
Q5P: U2.23 (16_A2_SCL0_Touch); also elsewhere on the board
Q6N: U2.41 (25_Touch_PWM); also elsewhere on the board
Q6P: U2.40 (24); also elsewhere on the board
Q7N: U2.43 (27_A16); also elsewhere on the board
Q7P: U2.42 (26_A15_RX2); also elsewhere on the board
Q8N: U2.45 (29_A18_SCL1); also elsewhere on the board
Q8P: U2.44 (28_A17); also elsewhere on the board
Q9N: U2.47 (31_A20_TX2); also elsewhere on the board
Q9P: U2.46 (30_A19_SDA1); also elsewhere on the board
Q10N: U2.49 (33_Touch); also elsewhere on the board
Q10P: U2.48 (32_Touch_PWM); also elsewhere on the board
RR0_MON: R53.2; also elsewhere on the board
SENSE_PULSE: U2.29 (22_A8_Touch_PWM); also elsewhere on the board
SENSE_RESET: U2.28 (21_A7_RX1_CS_PWM); also elsewhere on the board
SPARE_5: R43.1, U2.22 (15_A1_CS_Touch); also elsewhere on the board
SPARE_ADC_DAC: R53.1, U2.19 (A14/DAC); also elsewhere on the board
SPARE_ANA_6: R56.1, U2.37 (A11); also elsewhere on the board
SPARE_ANA_7: R55.1, U2.38 (A12); also elsewhere on the board
SPARE_ANA_8: R54.1, U2.51 (A13); also elsewhere on the board
SPI_CLK: U2.20 (13_LED_SCK); also elsewhere on the board
SPI_SDI: U2.14 (12_DIN); also elsewhere on the board
SPI_SDO: U2.13 (11_DOUT); also elsewhere on the board
TC0_MON: R56.2; also elsewhere on the board
TEENSY_3V3: R5.1, U2.16 (3.3V), U2.31 (3.3V_max100mA), U2.35 (AREF), U2.50 (3.3V); also elsewhere on the board
TEENSY_VUSB: U2.34 (VUSB); also elsewhere on the board

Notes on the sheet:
CORE 64 INTERACTIVE CORE MEMORY BADGE V0.5 LOGIC BOARD
Reads 1/4 voltage of +VSW (after RPP) before regulators.
Teensy LC has incoming USB power/programming on board.
TEENSY 3.2 MCU CONNECTIONS
BOM TO DO: TEENSY requires at least three headers that do not get auto populated in the BOM from KiCAD.
*** MUST CUT THE USB-VIN on back of TEENSY 3.2 ***
All non-polarized capacitors are X7R or X5R ceramic unless otherwise noted.
Teensy 3V3 is only used for AREF and TeensyView. Current is limited, do not use for anything else.
PRIMARY USE 1 Core Plane
3.2” TFT as LED Array Replacement [OPTIONAL]
8 Core Plane Selector [OPTIONAL] Requires other modifications.
SILKSCREEN BACK
SILKSCREEN UNDER TEENSY: CUT VIN-BUSB
To use the Teensy 3.2 RTC you must add two things: 1) Crystal: 32.768 kHz, 12.5 pF Citizen CFS-206, Digi-Key 300-8763-ND (5ppm) (on bottom side of the Teensy board, not shown in this schematic) 2) Battery Holder: MPD BC-2003, Digi-Key BC-2003-TR-CT-ND 3) Battery: 3V CR2032 Digi-Key P189-ND (battery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
SILKSCREEN: RTC BAT. CR2032
SILKSCREEN FRONT
Core 64 Logo Interactive Core Memory QR Code Maker Website RTC Battery CR2032 PCB Maker Assembler Serial Number P/N REV
Interactive Core Memory All logic is 3V3 Level
Spare Analog
Spare IO
SPI Devices [OPTIONAL]
RTC CLOCK BATTERY [OPTIONAL]
I2C here, there, and everywhere.
Because VIN-VUSB is cut on the back of the Teensy, power into the Teensy’s USB port is routed in this order: TEENSY VUSB -> ON/OFF & LIPO -> 5V REG -> TEENSY VIN
Left Edge
Bottom Edge
Right Edge
Back 1x4
Back L7
Back R7
QxP (PNP) is normally high, low to activate matrix transistor. QxN (NPN) is normally low, high to activate matrix transistor.
3.6-6.0V
All analog-only pins (A10-A14), AREF, Program and Reset are 3.3V only.
